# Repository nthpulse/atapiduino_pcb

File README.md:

# atapiduino_pcb
PCB for Carlos Durandal's Atapiduino project

Gerbers are in the atapiduino.zip file.

All credit for the original project, schematics and firmware goes to Carlos Durandal:
http://singlevalve.web.fc2.com/Atapiduino/atapiduino.htm

All I did was make this PCB for the project.

http://nthpulse.net/projects/atapiduino_pcb

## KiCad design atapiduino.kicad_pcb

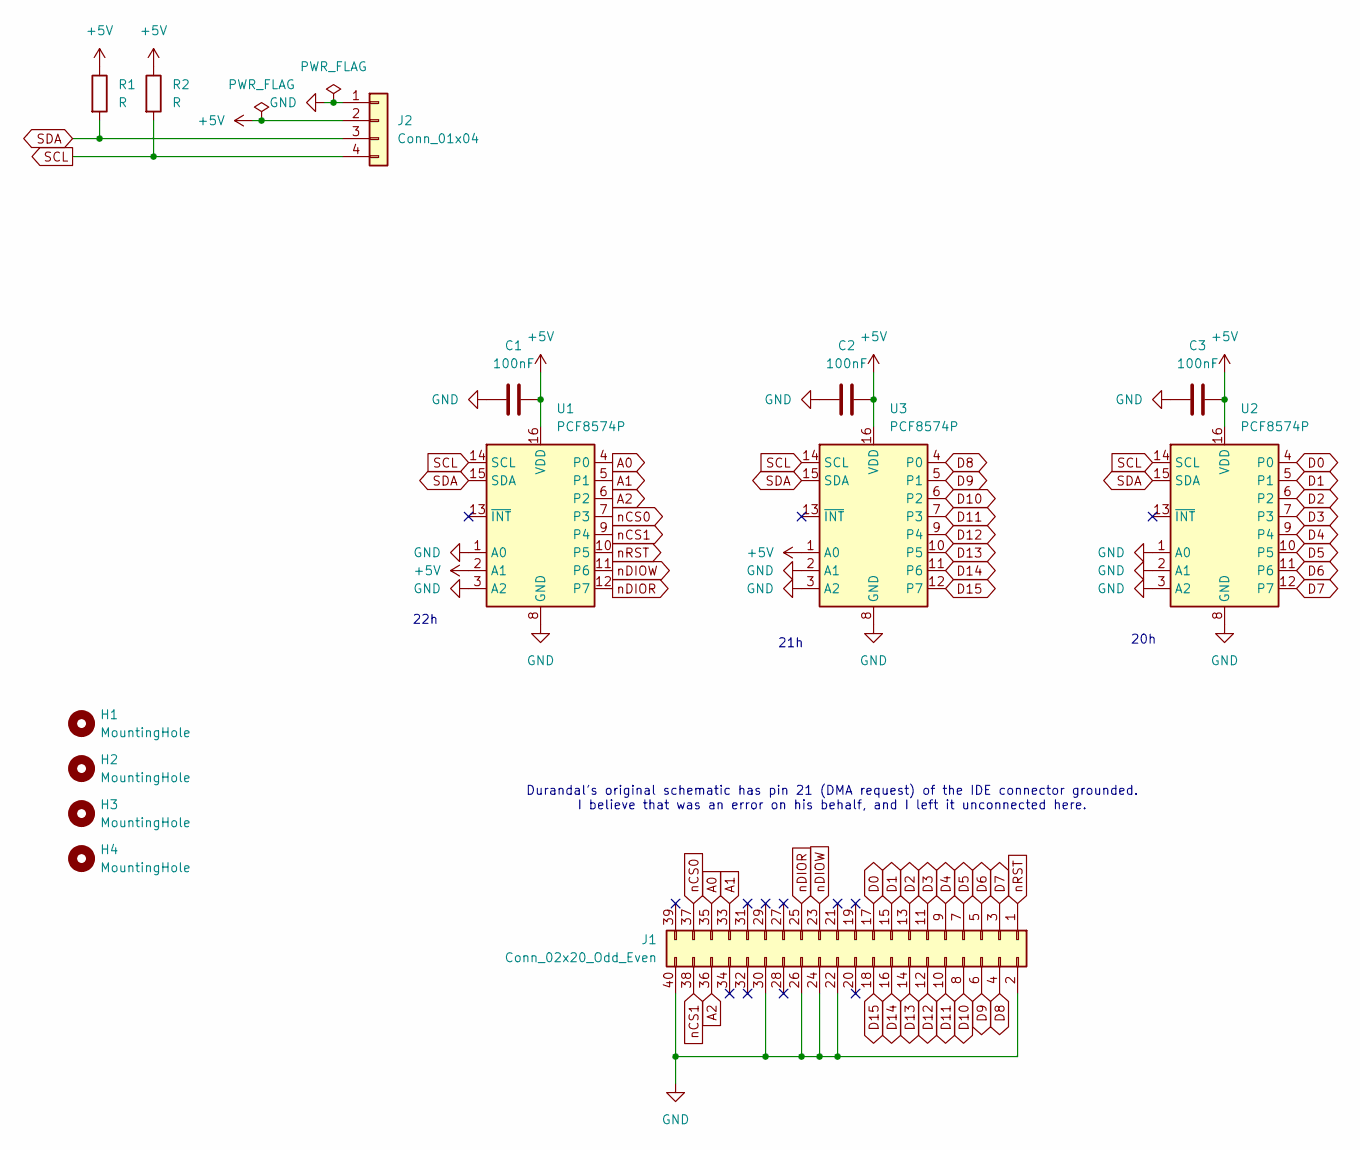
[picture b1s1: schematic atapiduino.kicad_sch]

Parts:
C1, C2, C3: 100nF; C_Disc_D3.0mm_W1.6mm_P2.50mm
H1, H2, H3, H4: MountingHole; MountingHole_3.2mm_M3
J1: Conn_02x20_Odd_Even; IDC-Header_2x20_P2.54mm_Vertical
J2: Conn_01x04; PinHeader_1x04_P2.54mm_Vertical
R1, R2: R; R_Axial_DIN0207_L6.3mm_D2.5mm_P10.16mm_Horizontal
U1, U2, U3: PCF8574P; DIP-16_W7.62mm

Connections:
+5V: C1.1, C2.1, C3.1, J2.2, R1.1, R2.1, U1.2 (A1), U1.16 (VDD), U2.16 (VDD), U3.1 (A0), U3.16 (VDD)
A0: J1.35, U1.4 (P0)
A1: J1.33, U1.5 (P1)
A2: J1.36, U1.6 (P2)
D0: J1.17, U2.4 (P0)
D1: J1.15, U2.5 (P1)
D2: J1.13, U2.6 (P2)
D3: J1.11, U2.7 (P3)
D4: J1.9, U2.9 (P4)
D5: J1.7, U2.10 (P5)
D6: J1.5, U2.11 (P6)
D7: J1.3, U2.12 (P7)
D8: J1.4, U3.4 (P0)
D9: J1.6, U3.5 (P1)
D10: J1.8, U3.6 (P2)
D11: J1.10, U3.7 (P3)
D12: J1.12, U3.9 (P4)
D13: J1.14, U3.10 (P5)
D14: J1.16, U3.11 (P6)
D15: J1.18, U3.12 (P7)
GND: C1.2, C2.2, C3.2, J1.2, J1.22, J1.24, J1.26, J1.30, J1.40, J2.1, U1.1 (A0), U1.3 (A2), U1.8 (GND), U2.1 (A0), U2.2 (A1), U2.3 (A2), U2.8 (GND), U3.2 (A1), U3.3 (A2), U3.8 (GND)
SCL: J2.4, R2.2, U1.14 (SCL), U2.14 (SCL), U3.14 (SCL)
SDA: J2.3, R1.2, U1.15 (SDA), U2.15 (SDA), U3.15 (SDA)
nCS0: J1.37, U1.7 (P3)
nCS1: J1.38, U1.9 (P4)
nDIOR: J1.25, U1.12 (P7)
nDIOW: J1.23, U1.11 (P6)
nRST: J1.1, U1.10 (P5)

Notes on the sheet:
Durandal's original schematic has pin 21 (DMA request) of the IDE connector grounded. I believe that was an error on his behalf, and I left it unconnected here.
21h
20h
22h

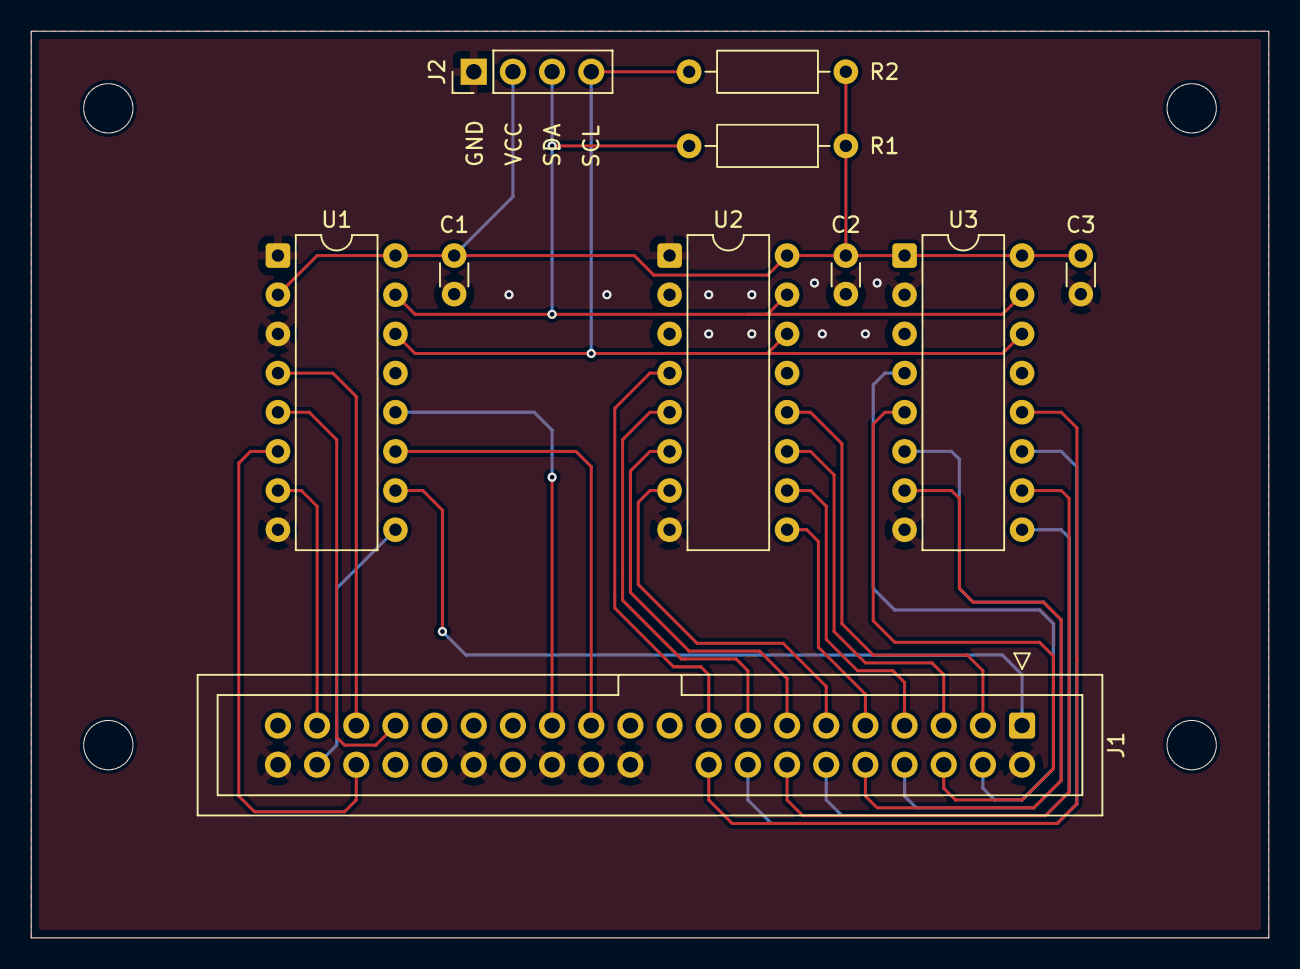
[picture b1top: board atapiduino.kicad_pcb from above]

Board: 2 copper layers, 80.3 x 58.8 mm, 14 parts (0 on the bottom side), 28 nets.
